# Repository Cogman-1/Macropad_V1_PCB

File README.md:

# Macropad V1 — Hardware

Custom 9-key USB macropad designed using KiCad, based on an STM32G4 microcontroller.

> **Project Status: Early Development / Prototype**
>
> Macropad V1 is currently in its first hardware revision. The design is subject to changes as development and testing progress.

## Overview

Macropad V1 is a custom-designed USB macropad intended to provide programmable buttons and LED indicators through a dedicated host application.

The project focuses on developing a compact, extensible hardware platform with custom firmware and software.

The device communicates with the host using USB 2.0 Full Speed, with a vendor-defined HID interface.

## Hardware Specifications

| Component               | Description                  |
| ----------------------- | ---------------------------- |
| Microcontroller         | STM32G4 Series               |
| USB Interface           | USB 2.0 Full Speed           |
| Connector               | USB Type-C                   |
| Buttons                 | 9 mechanical switches        |
| LEDs                    | 9 reverse-mounted green LEDs |
| Power Supply            | USB 5V / 3.3V LDO regulator  |
| Programming & Debugging | SWD (Tag-Connect)            |
| PCB                     | 2-layer custom PCB           |
| Design Software         | KiCad 9                      |

### Main Features

- Custom-designed PCB and schematic
- 9 individually readable mechanical switches
- 9 independently controllable LEDs
- USB-C connectivity
- On-board 3.3V voltage regulation
- USB ESD protection
- SWD interface for programming and debugging
- Designed for automated PCB assembly where applicable

## PCB Design

The PCB was designed in **KiCad 9**.

The design uses two copper layers and includes dedicated power distribution, ground planes and decoupling capacitors for the STM32 microcontroller.

Some components, including the mechanical switches, are intended for manual assembly.

Manufacturing and assembly are planned around JLCPCB services.

## Repository Contents

This repository contains the hardware design files required to inspect, modify and manufacture the PCB.

These include:

- KiCad project files
- Circuit schematic
- PCB layout
- Component footprints and related design files

### Opening the Project

1. Install KiCad 9 or a compatible version.
2. Clone this repository.
3. Open the `.kicad_pro` project file.
4. Open the schematic or PCB editor as required.

## Firmware & Software

Macropad V1 uses custom firmware developed for the STM32G4 platform.

The firmware is responsible for:

- Reading button states
- Controlling individual LEDs
- Managing USB HID communication
- Exchanging data with the host computer

[Firmware Repository Link](https://github.com/Cogman-1/Macropad_V1_src)

A separate host application is planned to provide configurable button actions, macros and LED behavior.

The host software will consist of a background daemon and a configuration GUI.

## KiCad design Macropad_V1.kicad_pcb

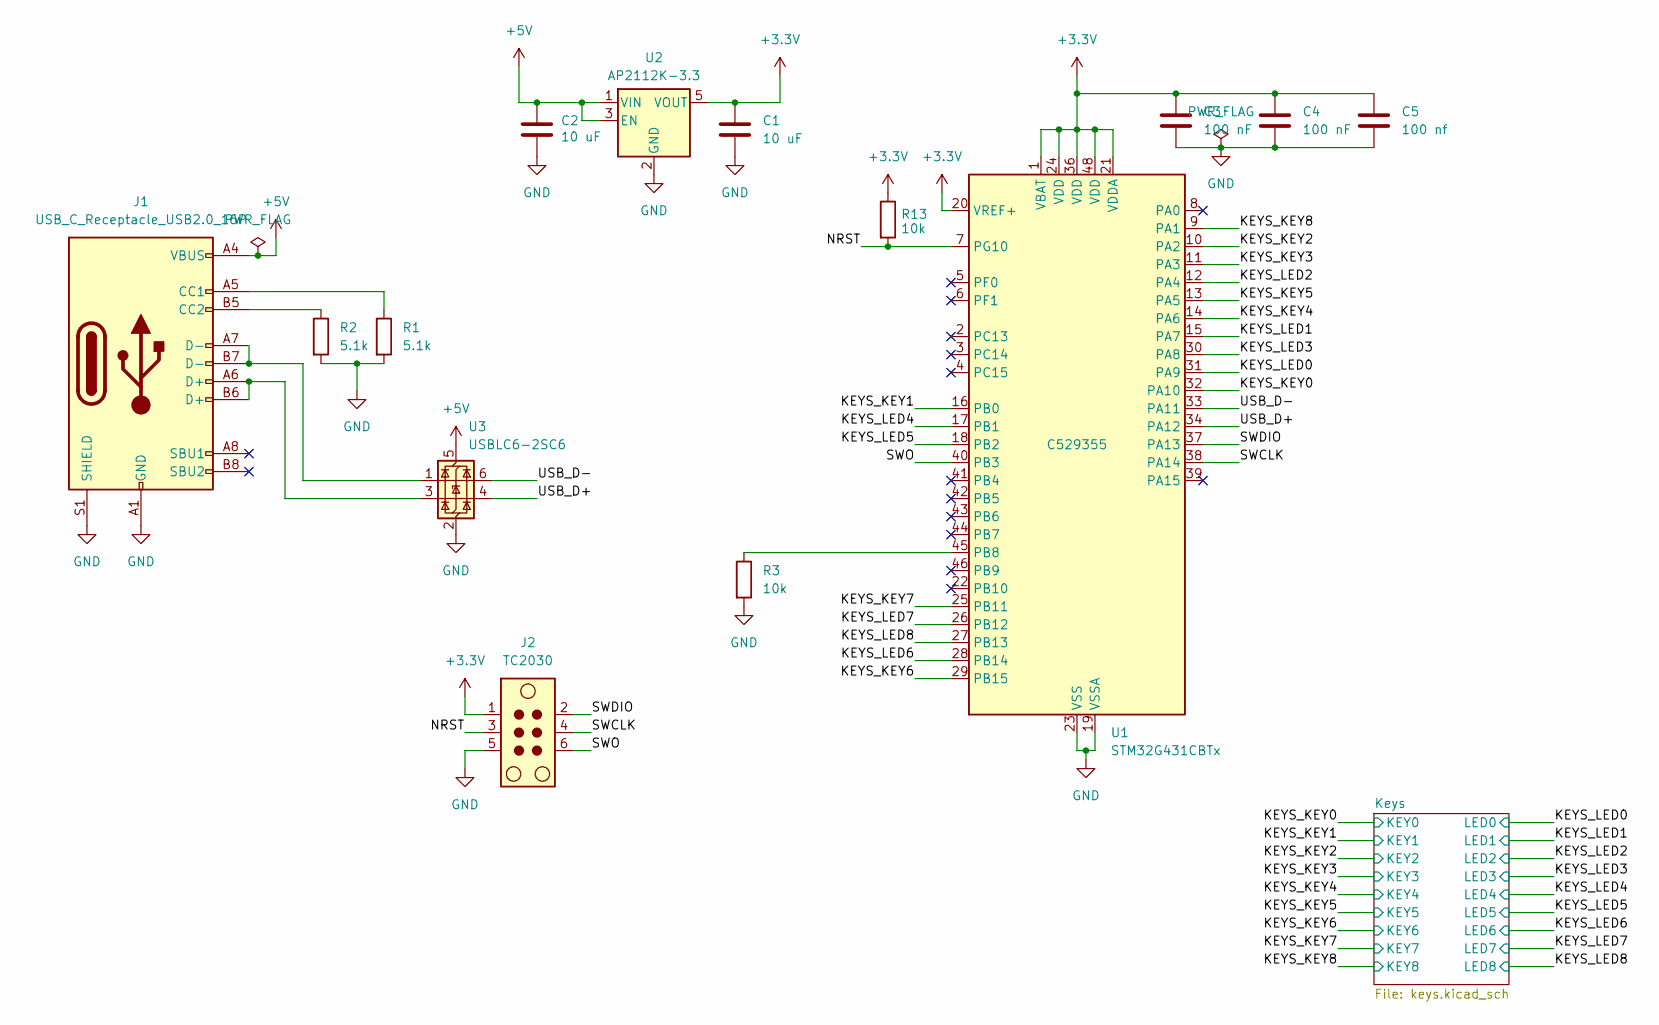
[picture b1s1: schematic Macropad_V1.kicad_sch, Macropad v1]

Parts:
C1, C2: 10 uF; C_0805_2012Metric; LCSC C15850
C3, C4: 100 nF; C_0805_2012Metric; LCSC C28233
C5: 100 nf; C_0805_2012Metric; LCSC C28233
J1: USB_C_Receptacle_USB2.0_16P; USB_C_Receptacle_XKB_U262-16XN-4BVC11; LCSC C319148
J2: TC2030; Tag-Connect_TC2030-IDC-NL_2x03_P1.27mm_Vertical
R1, R2: 5.1k; R_0805_2012Metric; LCSC C27834
R3, R13: 10k; R_0805_2012Metric; LCSC C17414
U1: STM32G431CBTx; LQFP-48_7x7mm_P0.5mm; LCSC C529355
U2: AP2112K-3.3; SOT-23-5; LCSC C51118
U3: USBLC6-2SC6; SOT-23-6; LCSC C7519

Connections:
+3.3V: C1.1, C3.1, C4.1, C5.1, J2.1, R13.1, U1.1 (VBAT), U1.20 (VREF+), U1.21 (VDDA), U1.24 (VDD), U1.36 (VDD), U1.48 (VDD), U2.5 (VOUT)
+5V: C2.1, J1.A4 (VBUS), J1.A9 (VBUS), J1.B4 (VBUS), J1.B9 (VBUS), U2.1 (VIN), U2.3 (EN), U3.5 (VBUS)
/KEYS_KEY0: U1.32 (PA10); also elsewhere on the board
/KEYS_KEY1: U1.16 (PB0); also elsewhere on the board
/KEYS_KEY2: U1.10 (PA2); also elsewhere on the board
/KEYS_KEY3: U1.11 (PA3); also elsewhere on the board
/KEYS_KEY4: U1.14 (PA6); also elsewhere on the board
/KEYS_KEY5: U1.13 (PA5); also elsewhere on the board
/KEYS_KEY6: U1.29 (PB15); also elsewhere on the board
/KEYS_KEY7: U1.25 (PB11); also elsewhere on the board
/KEYS_KEY8: U1.9 (PA1); also elsewhere on the board
/KEYS_LED0: U1.31 (PA9); also elsewhere on the board
/KEYS_LED1: U1.15 (PA7); also elsewhere on the board
/KEYS_LED2: U1.12 (PA4); also elsewhere on the board
/KEYS_LED3: U1.30 (PA8); also elsewhere on the board
/KEYS_LED4: U1.17 (PB1); also elsewhere on the board
/KEYS_LED5: U1.18 (PB2); also elsewhere on the board
/KEYS_LED6: U1.28 (PB14); also elsewhere on the board
/KEYS_LED7: U1.26 (PB12); also elsewhere on the board
/KEYS_LED8: U1.27 (PB13); also elsewhere on the board
/NRST: J2.3, R13.2, U1.7 (PG10)
/SWCLK: J2.4, U1.38 (PA14)
/SWDIO: J2.2, U1.37 (PA13)
/SWO: J2.6, U1.40 (PB3)
/USB_D+: U1.34 (PA12), U3.4 (I/O2)
/USB_D-: U1.33 (PA11), U3.6 (I/O1)
GND: C1.2, C2.2, C3.2, C4.2, C5.2, J1.A1 (GND), J1.A12 (GND), J1.B1 (GND), J1.B12 (GND), J1.S1 (SHIELD), J2.5, R1.2, R2.2, R3.2, U1.19 (VSSA), U1.23 (VSS), U1.35 (VSS), U1.47 (VSS), U2.2 (GND), U3.2 (GND); also elsewhere on the board
unnamed: J1.A5 (CC1), R1.1
unnamed: J1.B5 (CC2), R2.1
unnamed: J1.A6 (D+), J1.B6 (D+), U3.3 (I/O2)
unnamed: J1.A7 (D-), J1.B7 (D-), U3.1 (I/O1)
unnamed: R3.1, U1.45 (PB8)

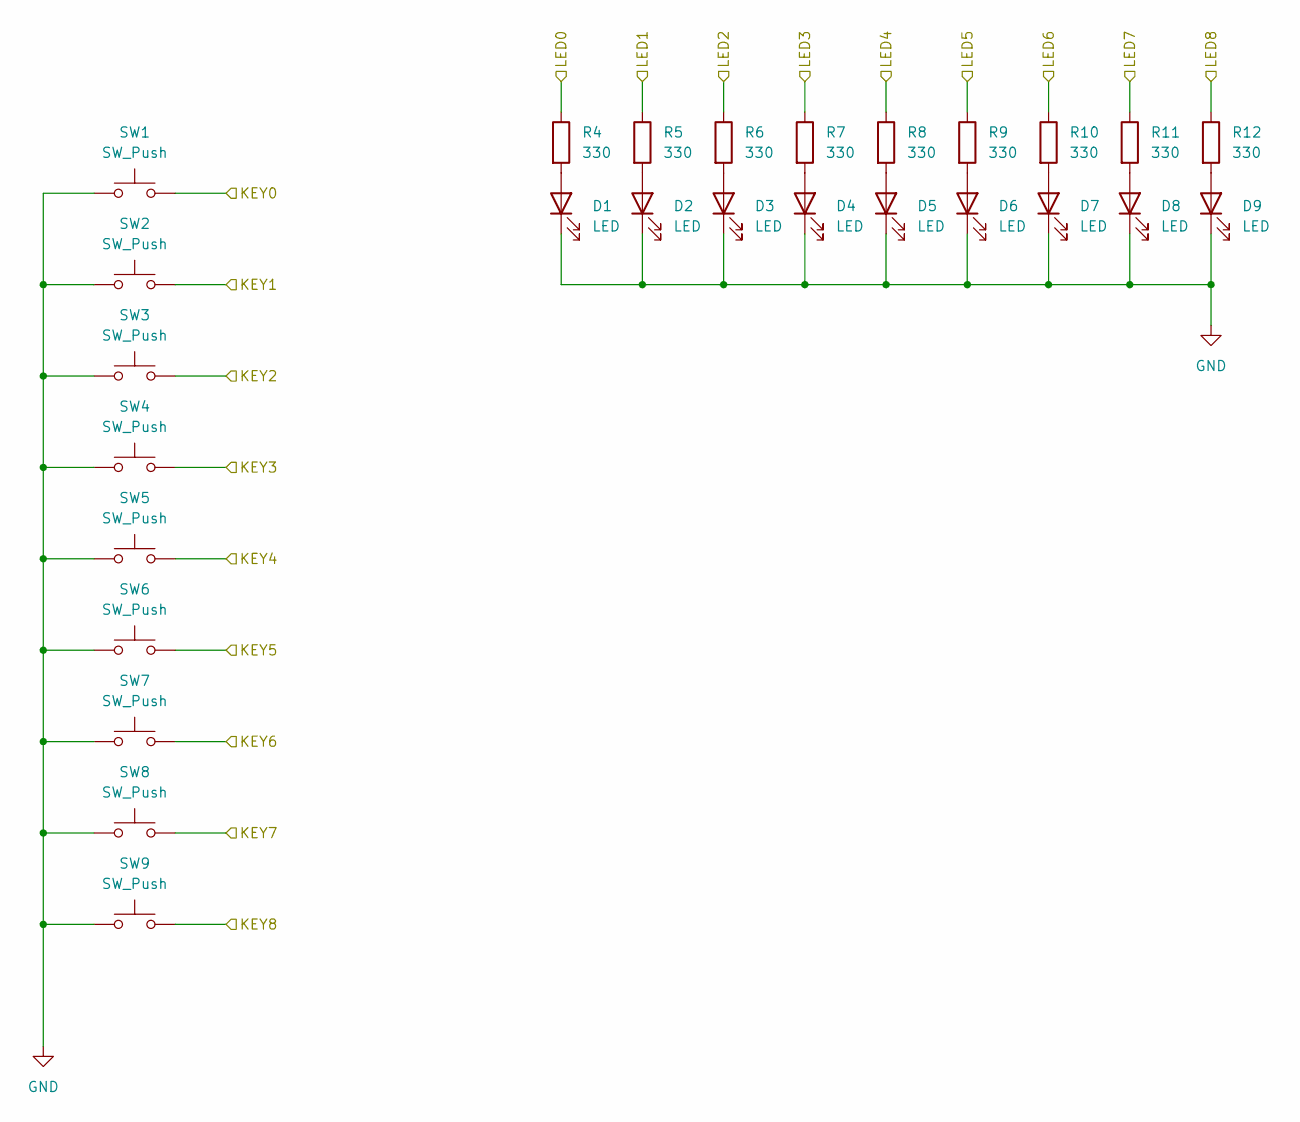
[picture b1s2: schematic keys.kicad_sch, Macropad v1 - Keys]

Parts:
D1, D2, D3, D4, D5, D6, D7, D8, D9: LED; LED_1206_3216Metric_ReverseMount_Hole1.8x2.4mm; LCSC C7496852
R4, R5, R6, R7, R8, R9, R10, R11, R12: 330; R_0805_2012Metric; LCSC C17630
SW1, SW2, SW3, SW4, SW5, SW6, SW7, SW8, SW9: SW_Push; SW_Cherry_MX_1.00u_PCB

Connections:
/KEYS_KEY0: SW1.2; also elsewhere on the board
/KEYS_KEY1: SW2.2; also elsewhere on the board
/KEYS_KEY2: SW3.2; also elsewhere on the board
/KEYS_KEY3: SW4.2; also elsewhere on the board
/KEYS_KEY4: SW5.2; also elsewhere on the board
/KEYS_KEY5: SW6.2; also elsewhere on the board
/KEYS_KEY6: SW7.2; also elsewhere on the board
/KEYS_KEY7: SW8.2; also elsewhere on the board
/KEYS_KEY8: SW9.2; also elsewhere on the board
/KEYS_LED0: R4.1; also elsewhere on the board
/KEYS_LED1: R5.1; also elsewhere on the board
/KEYS_LED2: R6.1; also elsewhere on the board
/KEYS_LED3: R7.1; also elsewhere on the board
/KEYS_LED4: R8.1; also elsewhere on the board
/KEYS_LED5: R9.1; also elsewhere on the board
/KEYS_LED6: R10.1; also elsewhere on the board
/KEYS_LED7: R11.1; also elsewhere on the board
/KEYS_LED8: R12.1; also elsewhere on the board
GND: D1.1 (K), D2.1 (K), D3.1 (K), D4.1 (K), D5.1 (K), D6.1 (K), D7.1 (K), D8.1 (K), D9.1 (K), SW1.1, SW2.1, SW3.1, SW4.1, SW5.1, SW6.1, SW7.1, SW8.1, SW9.1; also elsewhere on the board
unnamed: D1.2 (A), R4.2
unnamed: D2.2 (A), R5.2
unnamed: D3.2 (A), R6.2
unnamed: D4.2 (A), R7.2
unnamed: D5.2 (A), R8.2
unnamed: D6.2 (A), R9.2
unnamed: D7.2 (A), R10.2
unnamed: D8.2 (A), R11.2
unnamed: D9.2 (A), R12.2

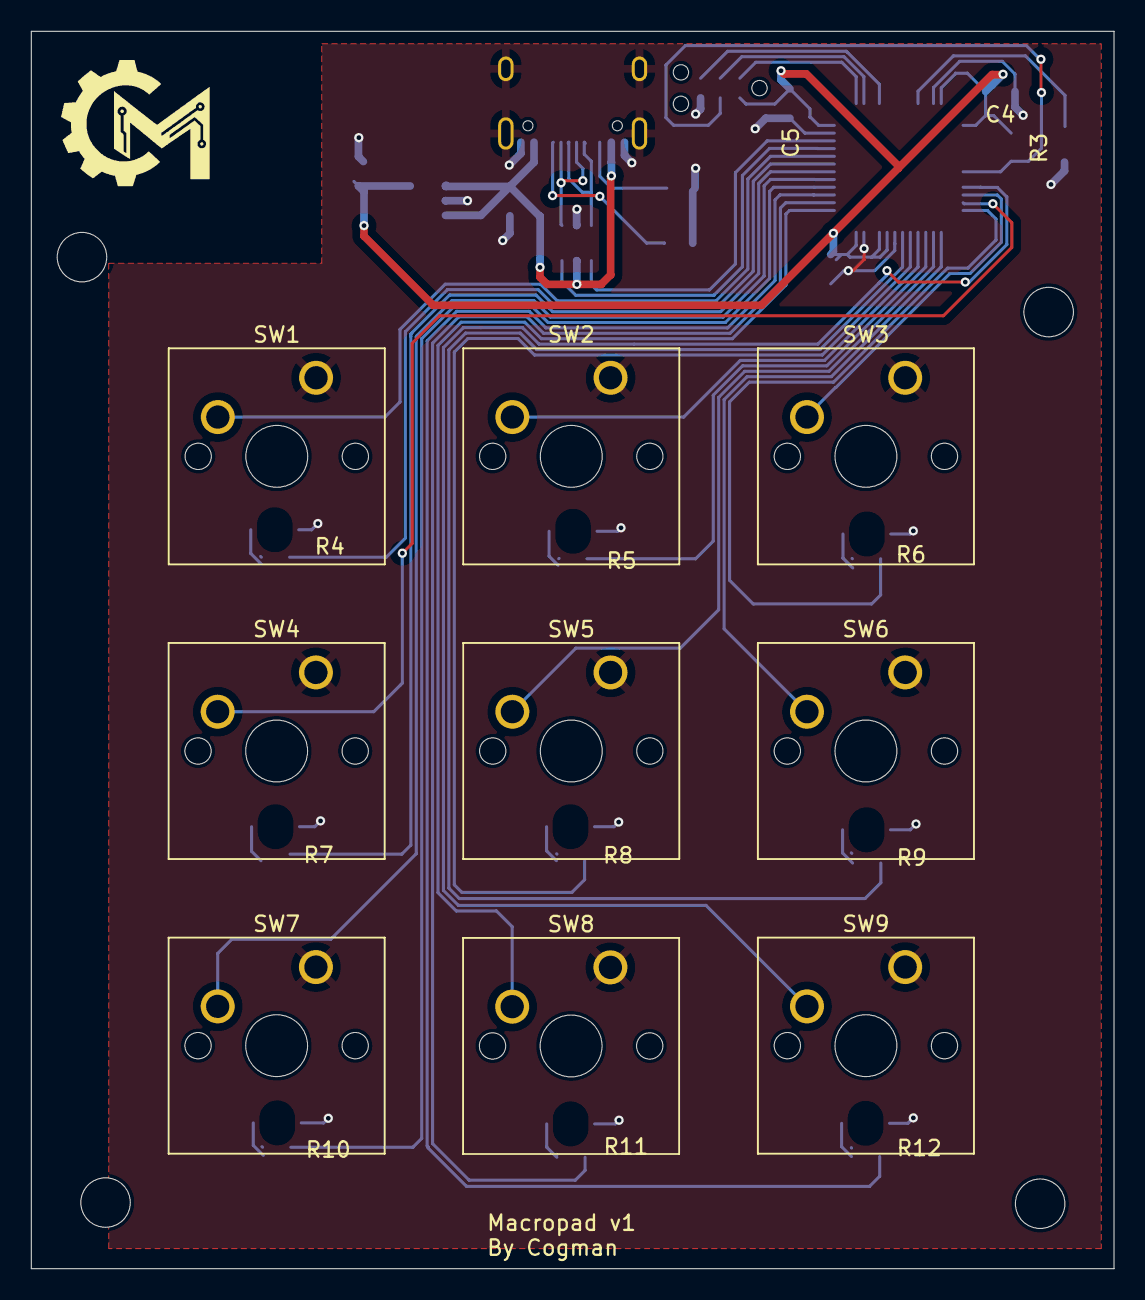
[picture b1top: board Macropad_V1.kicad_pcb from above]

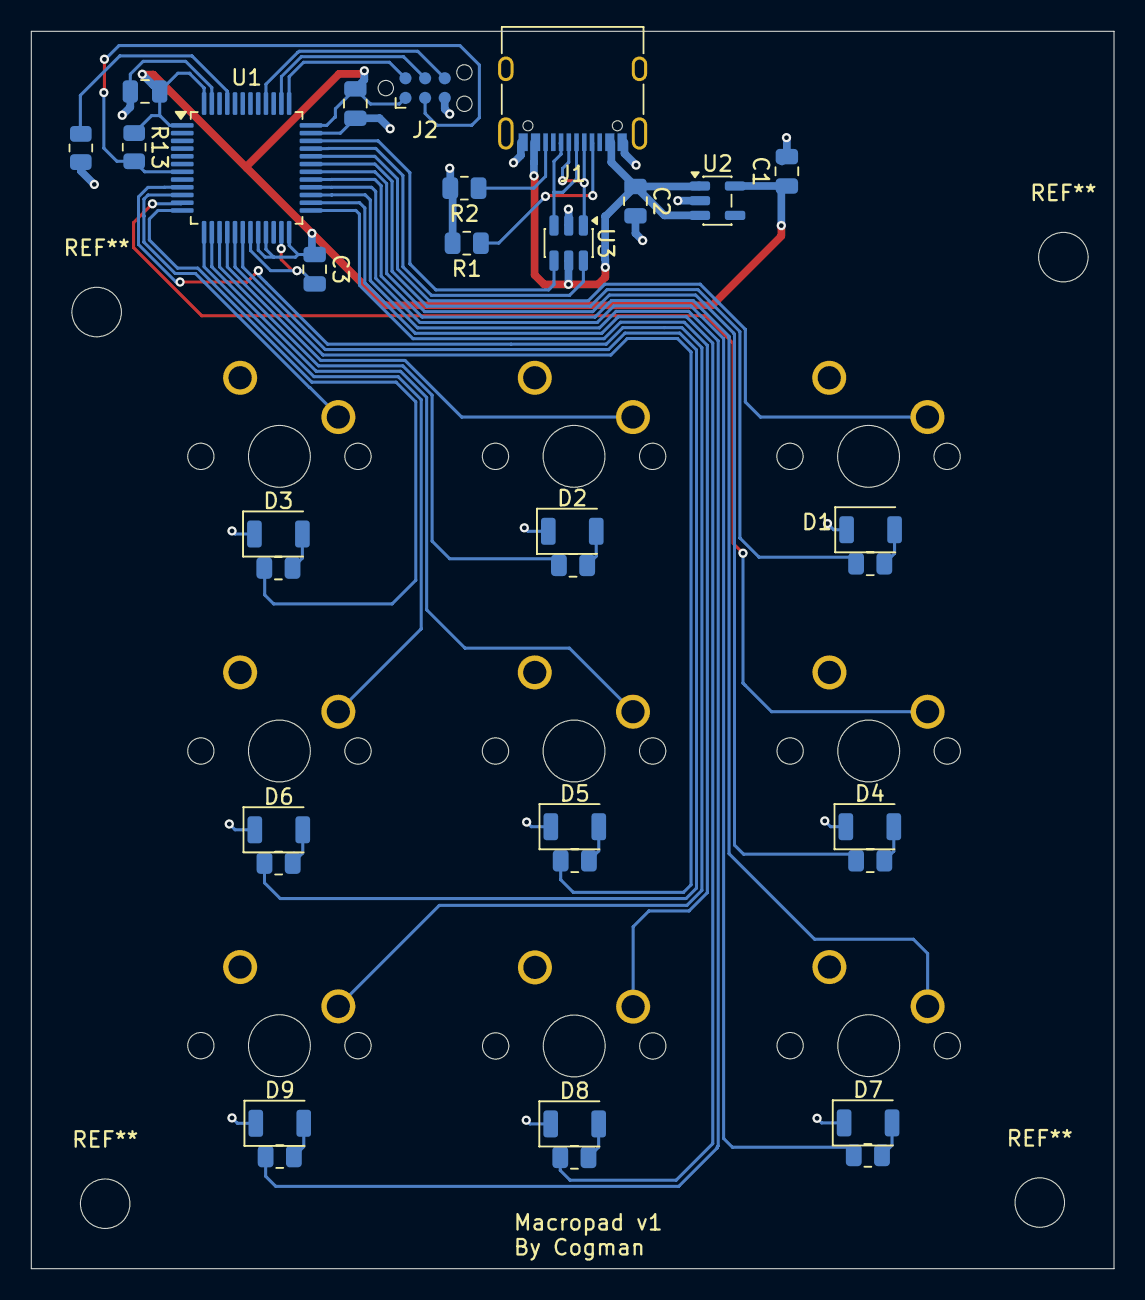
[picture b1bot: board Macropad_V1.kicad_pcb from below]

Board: 2 copper layers, 70.0 x 80.0 mm, 41 parts (32 on the bottom side), 41 nets.
